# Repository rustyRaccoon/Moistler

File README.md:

# Moistler
 Moisture sensor board with two LEDs for seriousness level

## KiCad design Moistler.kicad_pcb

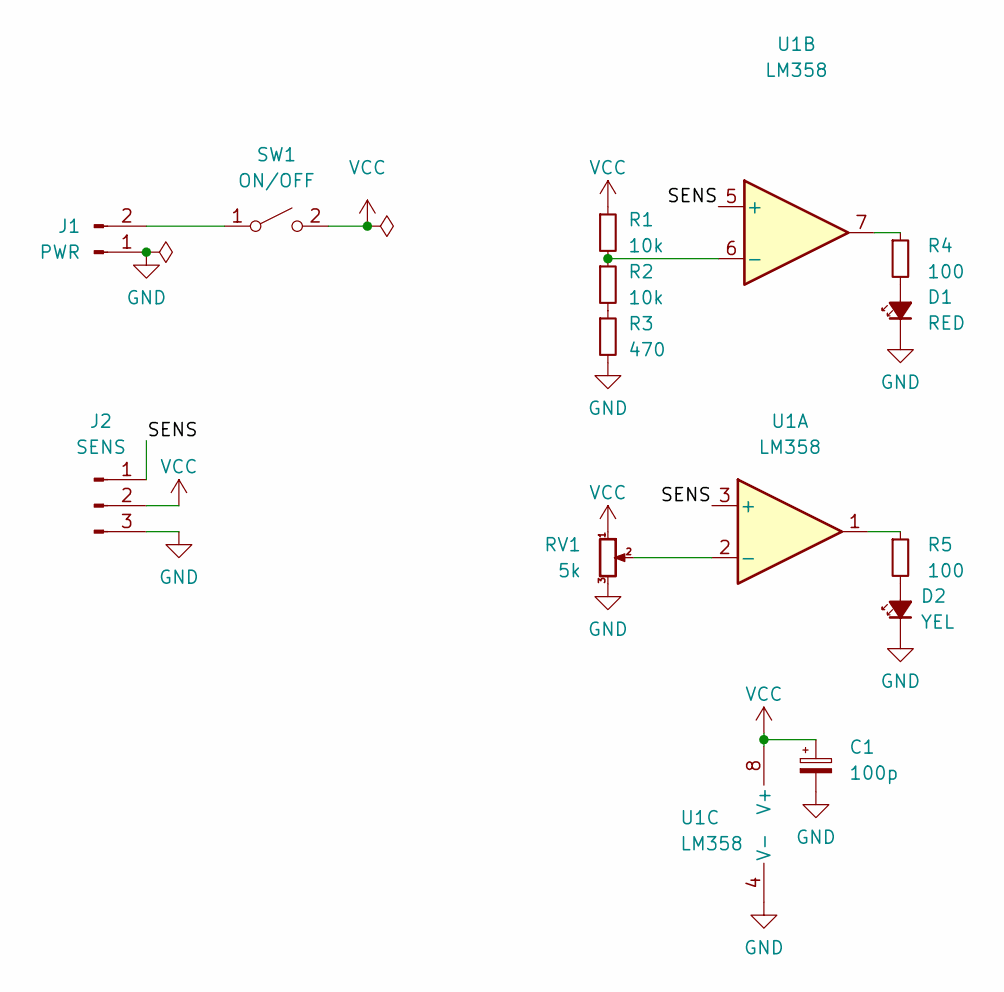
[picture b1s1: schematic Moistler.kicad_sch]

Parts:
C1: 100p; CP_Radial_D5.0mm_P2.50mm
D1: RED; LED_D5.0mm
D2: YEL; LED_D5.0mm
J1: PWR; PinHeader_1x02_P2.54mm_Horizontal
J2: SENS; PinHeader_1x03_P2.54mm_Horizontal
R1, R2: 10k; R_Axial_DIN0207_L6.3mm_D2.5mm_P7.62mm_Horizontal
R3: 470; R_Axial_DIN0207_L6.3mm_D2.5mm_P7.62mm_Horizontal
R4, R5: 100; R_Axial_DIN0207_L6.3mm_D2.5mm_P7.62mm_Horizontal
RV1: 5k; Potentiometer_ACP_CA9-H5_Horizontal
SW1: ON/OFF; R_Box_L8.4mm_W2.5mm_P5.08mm
U1: LM358; DIP-8_W7.62mm_Socket

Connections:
/SENS: J2.1, U1.3 (+), U1.5 (+)
GND: C1.2, D1.1 (K), D2.1 (K), J1.1, J2.3, R3.2, RV1.3, U1.4 (V-)
unnamed: D1.2 (A), R4.2
unnamed: D2.2 (A), R5.2
unnamed: J1.2, SW1.1 (A)
unnamed: R1.2, R2.1, U1.6 (-)
unnamed: R2.2, R3.1
unnamed: R4.1, U1.7
unnamed: R5.1, U1.1
unnamed: RV1.2, U1.2 (-)
VCC: C1.1, J2.2, R1.1, RV1.1, SW1.2 (B), U1.8 (V+)

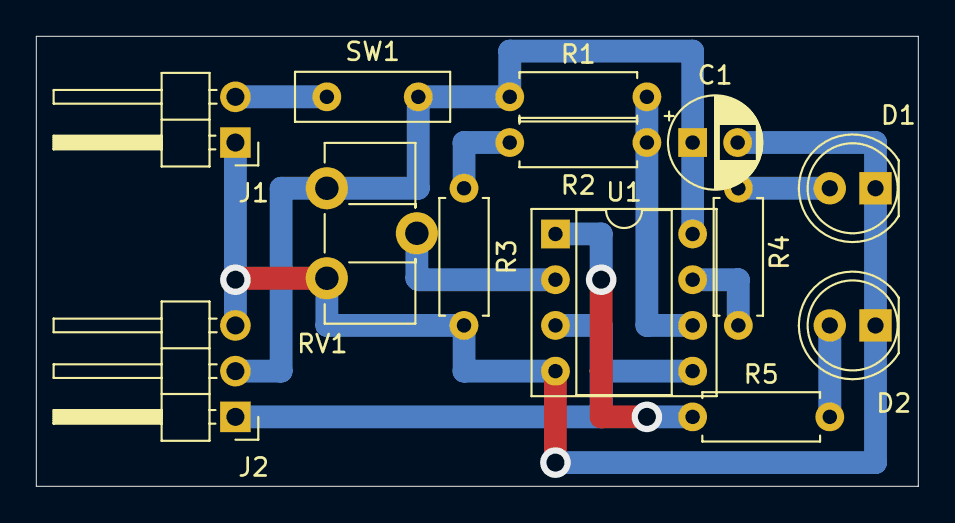
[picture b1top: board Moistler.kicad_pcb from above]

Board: 2 copper layers, 49.0 x 25.0 mm, 13 parts (0 on the bottom side), 11 nets.
